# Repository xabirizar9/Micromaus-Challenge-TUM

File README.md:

# Micromaus Best

## Development setup

## Useful Links

[Latex Document](https://latex.tum.de/7947285453qvwcngvsjpdx)

## Datasheets

[L298B](https://www.mouser.de/datasheet/2/389/cd00000240-1795236.pdf)

## Koordinatensysteme 
### Roboter
X zeigt nach vorne, Y nach links, Z nach oben.
Die Y-Achse ist die gemeinsame Drehachse der Motoren, der Ursprung liegt
in der Mitte.

### Welt
Das Weltkoordinatensystem hat seinen Ursprung bei der linken unteren Ecke.
Die X-Achse zeigt nach rechts, die Y-Ache nach oben und die Z-Achse aus
der Ebene heraus.

## Web Interface

To build and run web interface go to `./controller` director and run

```bash
cd ./controller
go build . && ./micromaus

```

Then you can visit the dashboard at [dashboard](http://localhot:8080)

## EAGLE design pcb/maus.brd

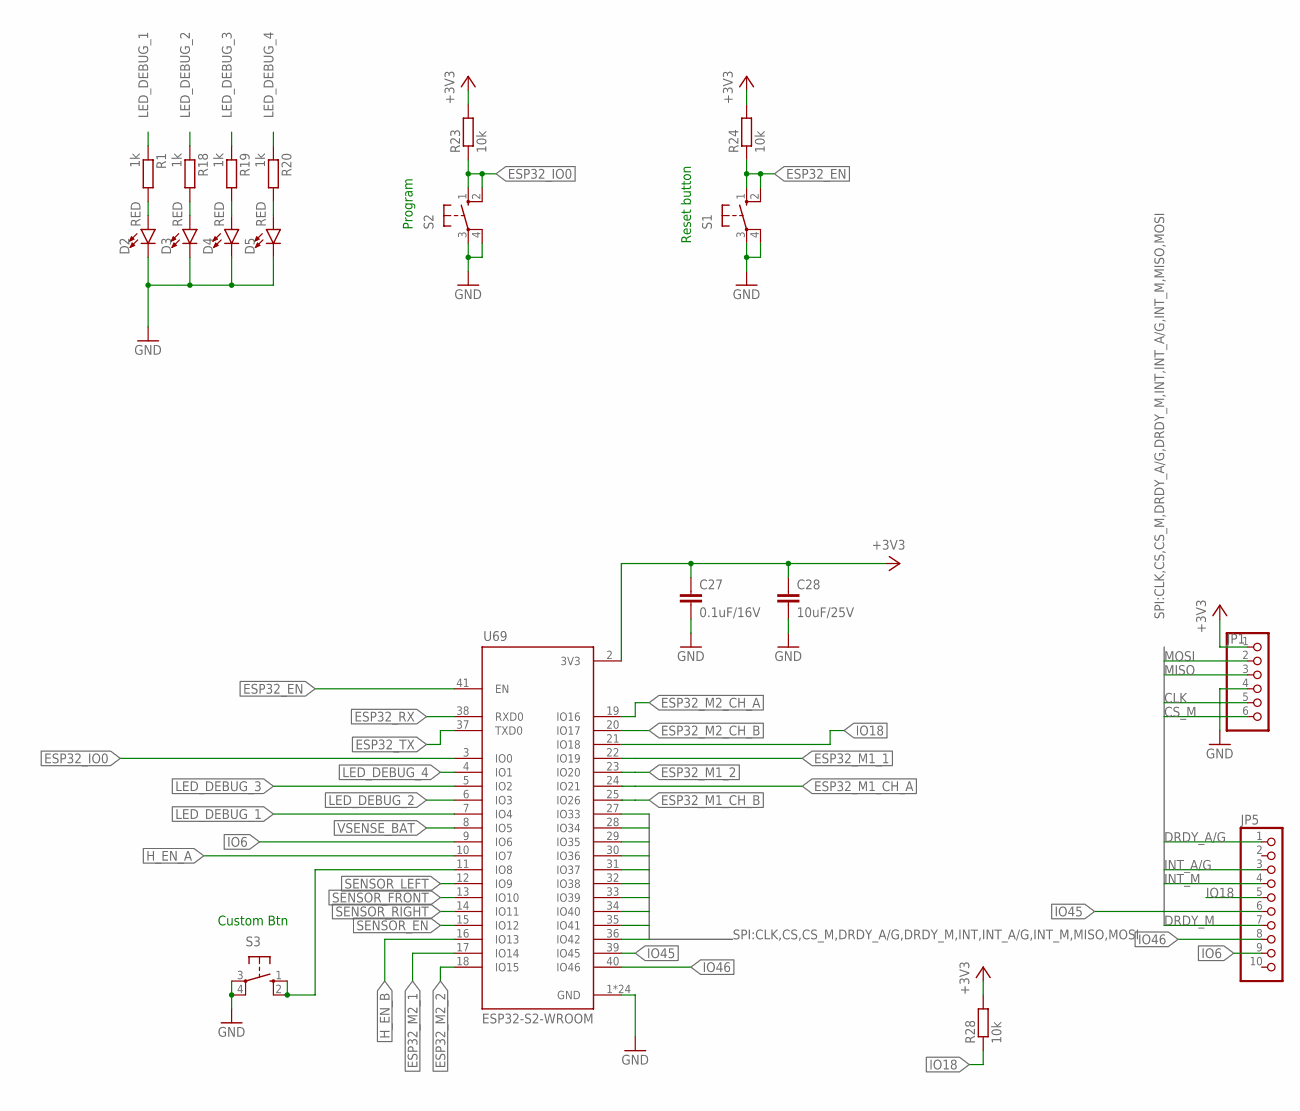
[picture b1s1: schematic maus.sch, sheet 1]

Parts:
C27: 0.1uF/16V; C0805
C28: 10uF/25V; C0805
D2, D3, D4, D5: RED; LED-1206
JP1: PINHD-1X6; 1X06
JP5: PINHD-1X10; 1X10
R1, R18, R19, R20: 1k; R0805
R23, R24, R28: 10k; R0805
S1, S2, S3: 10-XX; B3F-10XX
U69: ESP32-S2-WROOM; XCVR_ESP32-S2-WROOM

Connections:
+3V3: C27.1, C28.1, JP1.1, R23.2, R24.2, R28.2, U69.2 (3V3); also elsewhere on the board
CLK: JP1.5, U69.30 (IO36); also elsewhere on the board
CS: U69.28 (IO34); also elsewhere on the board
CS_M: JP1.6, U69.27 (IO33)
DRDY_A/G: JP5.1, U69.36 (IO42)
DRDY_M: JP5.7, U69.32 (IO38)
ESP32_EN: R24.1, S1.1 (S), S1.2 (S1), U69.41 (EN); also elsewhere on the board
ESP32_IO0: R23.1, S2.1 (S), S2.2 (S1), U69.3 (IO0); also elsewhere on the board
ESP32_M1_1: U69.22 (IO19); also elsewhere on the board
ESP32_M1_2: U69.23 (IO20); also elsewhere on the board
ESP32_M1_CH_A: U69.24 (IO21); also elsewhere on the board
ESP32_M1_CH_B: U69.25 (IO26); also elsewhere on the board
ESP32_M2_1: U69.17 (IO14); also elsewhere on the board
ESP32_M2_2: U69.18 (IO15); also elsewhere on the board
ESP32_M2_CH_A: U69.19 (IO16); also elsewhere on the board
ESP32_M2_CH_B: U69.20 (IO17); also elsewhere on the board
ESP32_RX: U69.38 (RXD0); also elsewhere on the board
ESP32_TX: U69.37 (TXD0); also elsewhere on the board
GND: C27.2, C28.2, D2.C, D3.C, D4.C, D5.C, JP1.4, S1.3, S1.4 (P1), S2.3, S2.4 (P1), S3.3, S3.4 (P1), U69.1 (GND), U69.26 (GND), U69.42 (GND), U69.43.1 (GND), U69.43.2 (GND), U69.43.3 (GND), U69.43.4 (GND), U69.43.5 (GND), U69.43.6 (GND), U69.43.7 (GND), U69.43.8 (GND), U69.43.9 (GND), U69.43.10 (GND), U69.43.11 (GND), U69.43.12 (GND), U69.43.13 (GND), U69.43.14 (GND), U69.43.15 (GND), U69.43.16 (GND), U69.43.17 (GND), U69.43.18 (GND), U69.43.19 (GND), U69.43.20 (GND), U69.43.21 (GND); also elsewhere on the board
H_EN_A: U69.10 (IO7); also elsewhere on the board
H_EN_B: U69.16 (IO13); also elsewhere on the board
INT: U69.33 (IO39); also elsewhere on the board
INT_A/G: JP5.3, U69.35 (IO41)
INT_M: JP5.4, U69.34 (IO40)
IO6: JP5.9, U69.9 (IO6)
IO18: JP5.5, R28.1, U69.21 (IO18)
IO45: JP5.6, U69.39 (IO45)
IO46: JP5.8, U69.40 (IO46)
LED_DEBUG_1: R1.1, U69.7 (IO4)
LED_DEBUG_2: R18.1, U69.6 (IO3)
LED_DEBUG_3: R19.1, U69.5 (IO2)
LED_DEBUG_4: R20.1, U69.4 (IO1)
MISO: JP1.3, U69.31 (IO37); also elsewhere on the board
MOSI: JP1.2, U69.29 (IO35); also elsewhere on the board
unnamed: S3.1 (S), S3.2 (S1), U69.11 (IO8)
unnamed: D2.A, R1.2
unnamed: D3.A, R18.2
unnamed: D4.A, R19.2
unnamed: D5.A, R20.2
SENSOR_EN: U69.15 (IO12); also elsewhere on the board
SENSOR_FRONT: U69.13 (IO10); also elsewhere on the board
SENSOR_LEFT: U69.12 (IO9); also elsewhere on the board
SENSOR_RIGHT: U69.14 (IO11); also elsewhere on the board
VSENSE_BAT: U69.8 (IO5); also elsewhere on the board

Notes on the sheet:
Reset button
Program
Custom Btn

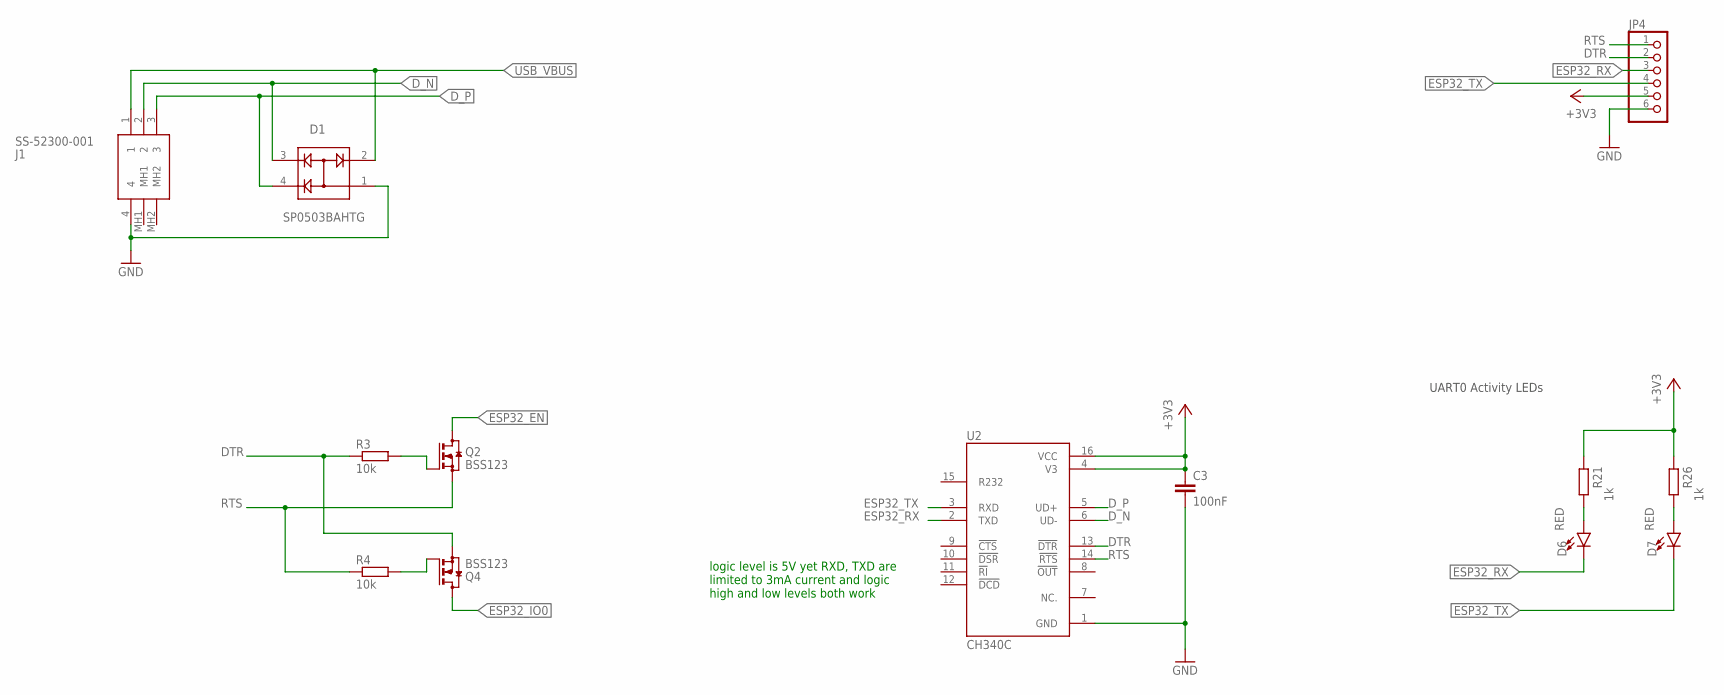
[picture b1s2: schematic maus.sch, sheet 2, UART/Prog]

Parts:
C3: 100nF; C0805
D1: SP0503BAHTG; SOT143
D6, D7: RED; LED-1206
J1: SS-52300-001; SS52300001
JP4: PINHD-1X6; 1X06
Q2, Q4: BSS123; SOT23
R3, R4: 10k; R0805
R21, R26: 1k; R0805
U2: CH340C; SOIC127P600X180-16N

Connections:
+3V3: C3.1, JP4.5, R21.2, R26.2, U2.4 (V3), U2.16 (VCC); also elsewhere on the board
DTR: JP4.2, Q4.2 (S), R3.1, U2.13 (!DTR)
D_N: D1.3, J1.2, U2.6 (UD-)
D_P: D1.4, J1.3, U2.5 (UD+)
ESP32_EN: Q2.3 (D); also elsewhere on the board
ESP32_IO0: Q4.3 (D); also elsewhere on the board
ESP32_RX: D6.C, JP4.3, U2.2 (TXD); also elsewhere on the board
ESP32_TX: D7.C, JP4.4, U2.3 (RXD); also elsewhere on the board
GND: C3.2, D1.1, J1.4, JP4.6, U2.1 (GND); also elsewhere on the board
unnamed: Q2.1 (G), R3.2
unnamed: Q4.1 (G), R4.2
unnamed: D6.A, R21.1
unnamed: D7.A, R26.1
RTS: JP4.1, Q2.2 (S), R4.1, U2.14 (!RTS)
USB_VBUS: D1.2, J1.1; also elsewhere on the board

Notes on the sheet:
UART0 Activity LEDs
logic level is 5V yet RXD, TXD are limited to 3mA current and logic high and low levels both work

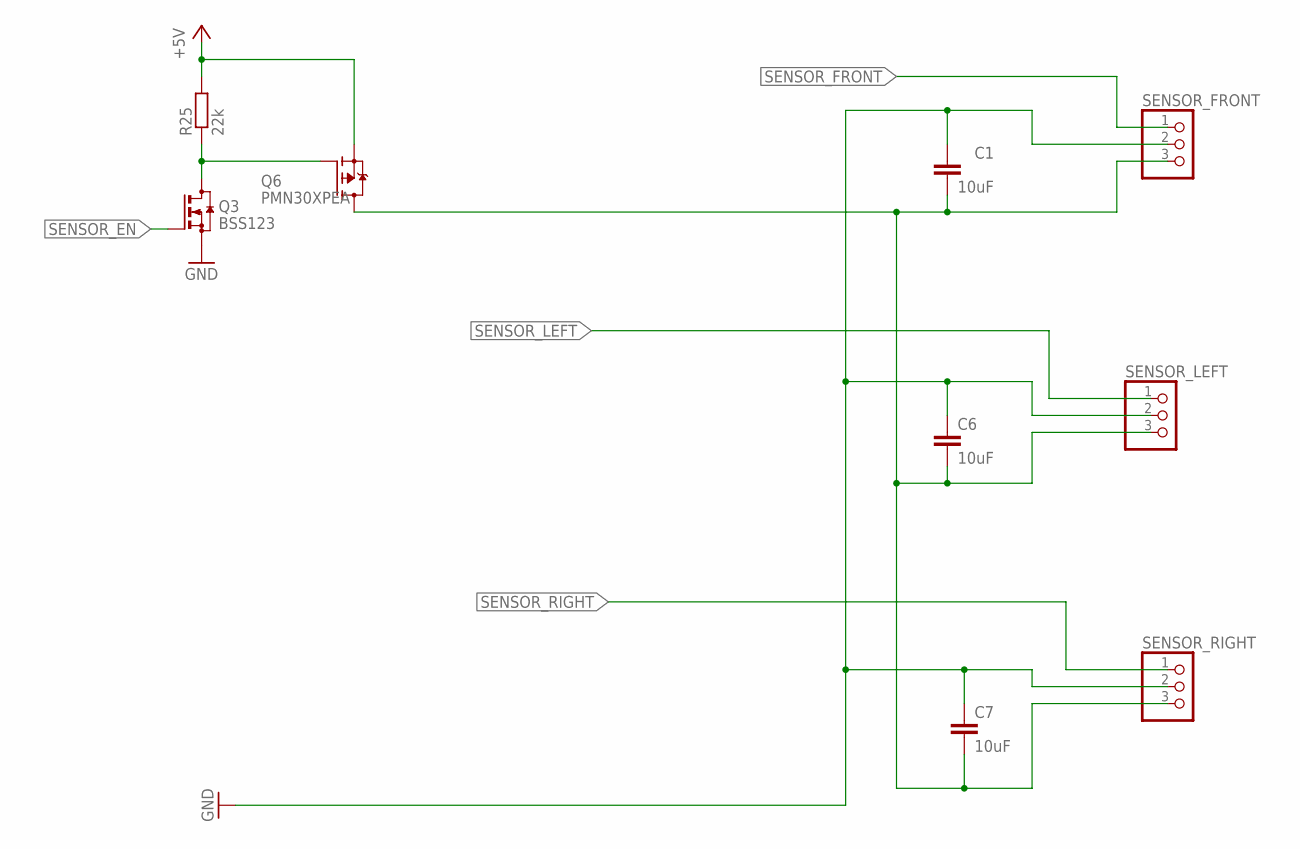
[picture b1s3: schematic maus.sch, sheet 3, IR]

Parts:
C1, C6, C7: 10uF; C0805
Q3: BSS123; SOT23
Q6: PMN30XPEA; SOT95P255X110-6N
R25: 22k; R0805
SENSOR_FRONT: PINHD-1X3; 1X03
SENSOR_LEFT: PINHD-1X3; 1X03
SENSOR_RIGHT: PINHD-1X3; 1X03

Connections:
+5V: Q6.4 (S), R25.2; also elsewhere on the board
GND: C1.1, C6.1, C7.1, Q3.2 (S), SENSOR_FRONT.2, SENSOR_LEFT.2, SENSOR_RIGHT.2; also elsewhere on the board
unnamed: Q3.3 (D), Q6.3 (G), R25.1
unnamed: C1.2, C6.2, C7.2, Q6.1 (D), Q6.2 (D), Q6.5 (D), Q6.6 (D), SENSOR_FRONT.3, SENSOR_LEFT.3, SENSOR_RIGHT.3
SENSOR_EN: Q3.1 (G); also elsewhere on the board
SENSOR_FRONT: SENSOR_FRONT.1; also elsewhere on the board
SENSOR_LEFT: SENSOR_LEFT.1; also elsewhere on the board
SENSOR_RIGHT: SENSOR_RIGHT.1; also elsewhere on the board

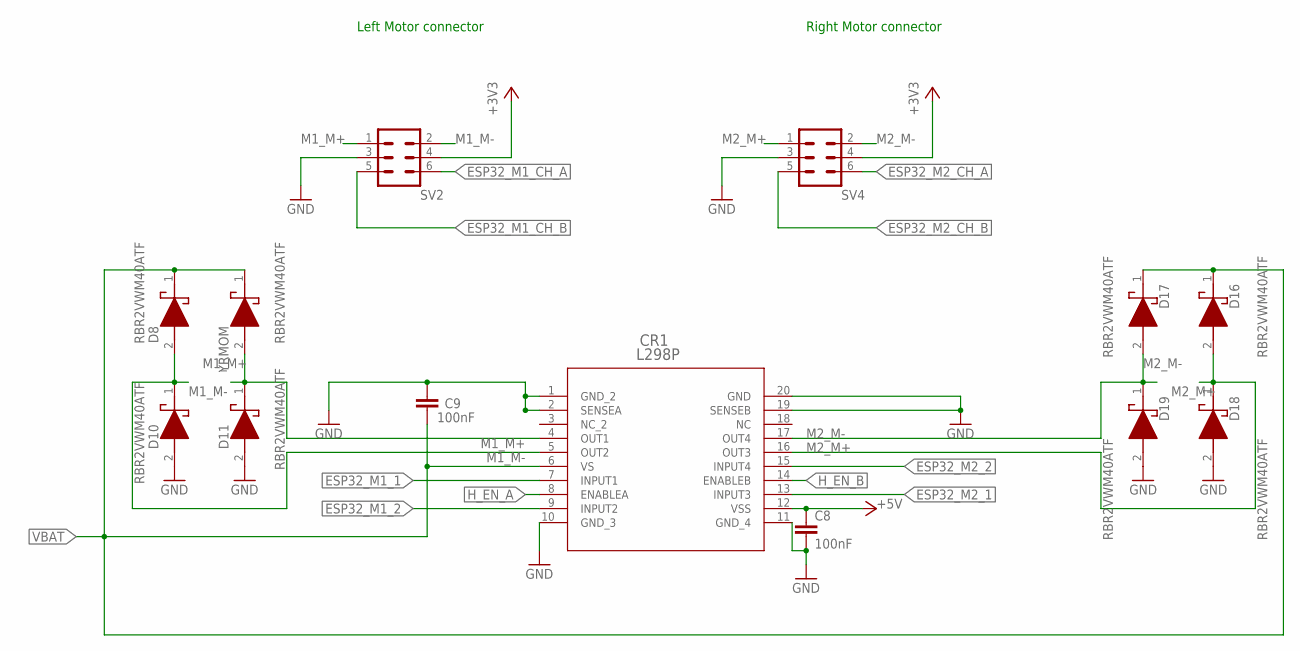
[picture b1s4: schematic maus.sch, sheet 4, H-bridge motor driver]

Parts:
C8, C9: 100nF; C0805
CR1: L298P; POWERSO-20_STM
D8, D10, D11, D16, D17, D18, D19: RBR2VWM40ATF; RB068VWM100
SV2, SV4: ML6
YRMOM: RBR2VWM40ATF; RB068VWM100

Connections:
+3V3: SV2.4, SV4.4; also elsewhere on the board
+5V: C8.1, CR1.12 (VSS); also elsewhere on the board
ESP32_M1_1: CR1.7 (INPUT1); also elsewhere on the board
ESP32_M1_2: CR1.9 (INPUT2); also elsewhere on the board
ESP32_M1_CH_A: SV2.6; also elsewhere on the board
ESP32_M1_CH_B: SV2.5; also elsewhere on the board
ESP32_M2_1: CR1.13 (INPUT3); also elsewhere on the board
ESP32_M2_2: CR1.15 (INPUT4); also elsewhere on the board
ESP32_M2_CH_A: SV4.6; also elsewhere on the board
ESP32_M2_CH_B: SV4.5; also elsewhere on the board
GND: C8.2, C9.2, CR1.1 (GND_2), CR1.2 (SENSEA), CR1.10 (GND_3), CR1.11 (GND_4), CR1.19 (SENSEB), CR1.20 (GND), D10.2 (A), D11.2 (A), D18.2 (A), D19.2 (A), SV2.3, SV4.3; also elsewhere on the board
H_EN_A: CR1.8 (ENABLEA); also elsewhere on the board
H_EN_B: CR1.14 (ENABLEB); also elsewhere on the board
M1_M+: CR1.4 (OUT1), D11.1 (K), SV2.1, YRMOM.2 (A)
M1_M-: CR1.5 (OUT2), D8.2 (A), D10.1 (K), SV2.2
M2_M+: CR1.16 (OUT3), D16.2 (A), D18.1 (K), SV4.1
M2_M-: CR1.17 (OUT4), D17.2 (A), D19.1 (K), SV4.2
VBAT: C9.1, CR1.6 (VS), D8.1 (K), D16.1 (K), D17.1 (K), YRMOM.1 (K); also elsewhere on the board

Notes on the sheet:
Left Motor connector
Right Motor connector

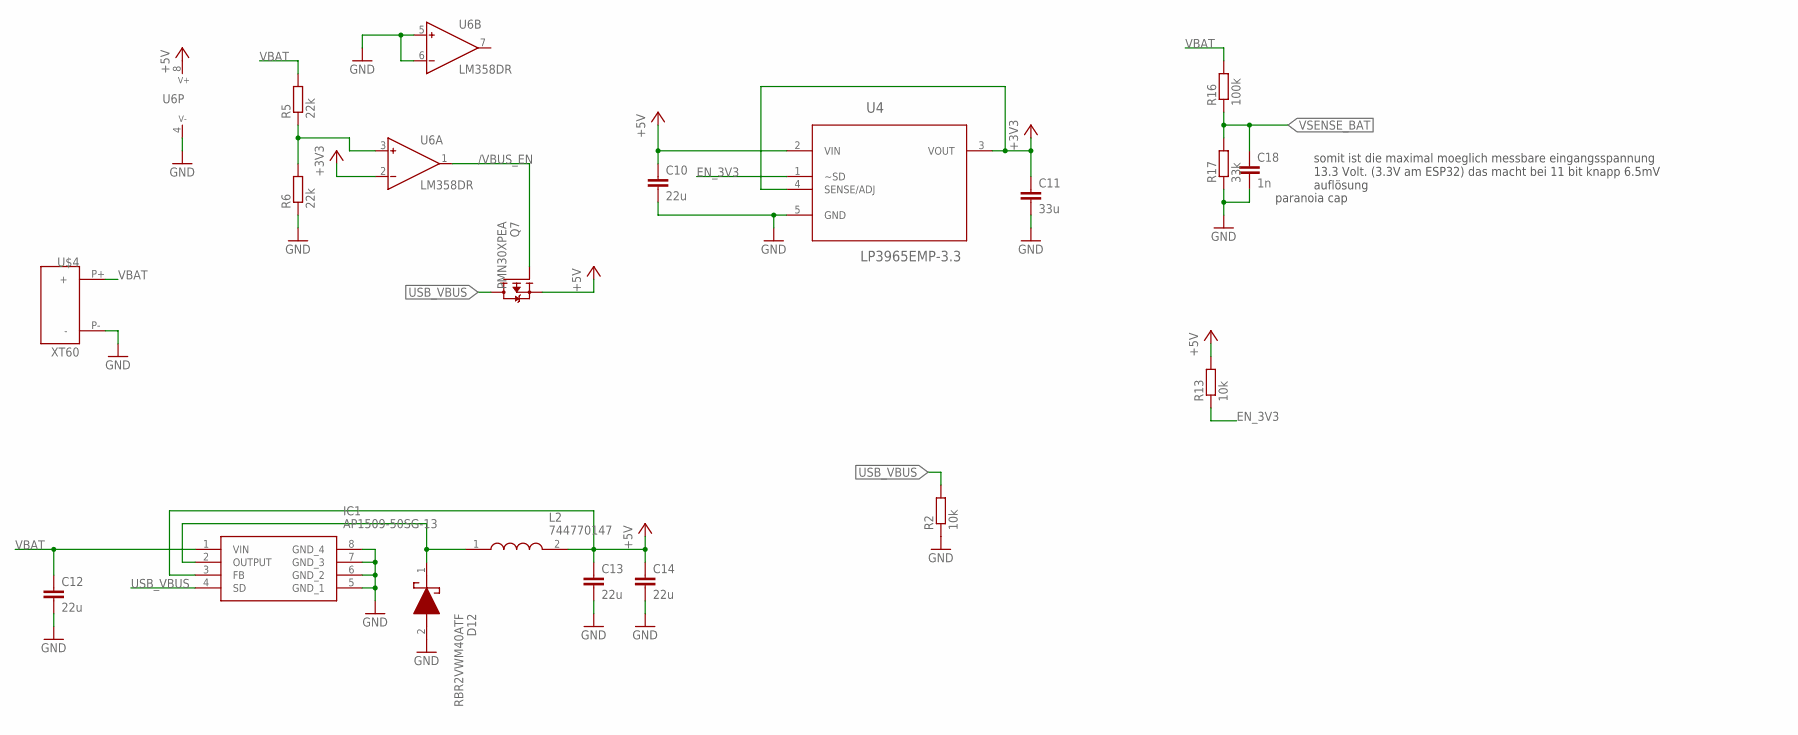
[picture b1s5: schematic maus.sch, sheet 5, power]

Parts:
C10, C12, C13, C14: 22u; C0805
C11: 33u; C0805
C18: 1n; C0805
D12: RBR2VWM40ATF; RB068VWM100
IC1: AP1509-50SG-13; SOIC127P600X175-8N
L2: 744770147; WE-PD_1260/1245/1280/121054
Q7: PMN30XPEA; SOT95P255X110-6N
R2, R13: 10k; R0805
R5, R6: 22k; R0805
R16: 100k; R0805
R17: 33k; R0805
U4: LP3965EMP-3.3; SOT150P696X180-5N
U6: LM358DR; SOIC127P610X175-8N
U$4: XT60; XT60-UPRIGHT

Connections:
+3V3: C11.1, U4.3 (VOUT), U4.4 (SENSE/ADJ), U6.2 (IN-); also elsewhere on the board
+5V: C10.1, C13.1, C14.1, IC1.3 (FB), L2.2, Q7.4 (S), R13.2, U4.2 (VIN), U6.8 (V+); also elsewhere on the board
/VBUS_EN: Q7.3 (G), U6.1 (OUT)
EN_3V3: R13.1, U4.1 (~SD)
GND: C10.2, C11.2, C12.2, C13.2, C14.2, C18.2, D12.2 (A), IC1.5 (GND_1), IC1.6 (GND_2), IC1.7 (GND_3), IC1.8 (GND_4), R2.1, R6.1, R17.1, U4.5 (GND), U6.4 (V-), U6.5 (IN+), U6.6 (IN-), U$4.P- (-); also elsewhere on the board
unnamed: D12.1 (K), IC1.2 (OUTPUT), L2.1
unnamed: R5.1, R6.2, U6.3 (IN+)
USB_VBUS: IC1.4 (SD), Q7.1 (D), Q7.2 (D), Q7.5 (D), Q7.6 (D), R2.2; also elsewhere on the board
VBAT: C12.1, IC1.1 (VIN), R5.2, R16.2, U$4.P+ (+); also elsewhere on the board
VSENSE_BAT: C18.1, R16.1, R17.2; also elsewhere on the board

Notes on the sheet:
somit ist die maximal moeglich messbare eingangsspannung 13.3 Volt. (3.3V am ESP32) das macht bei 11 bit knapp 6.5mV auflösung
paranoia cap

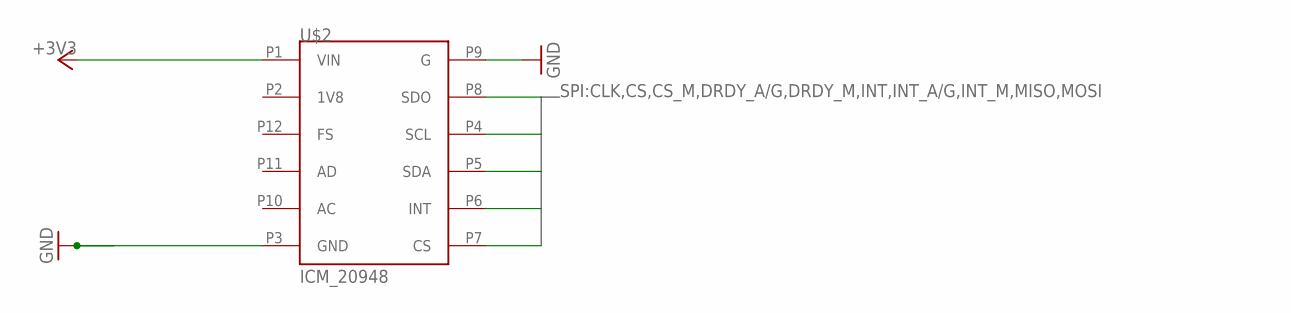
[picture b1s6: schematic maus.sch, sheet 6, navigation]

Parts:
U$2: ICM_20948; ICM_20948-F

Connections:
+3V3: U$2.P1 (VIN); also elsewhere on the board
CLK: U$2.P4 (SCL); also elsewhere on the board
CS: U$2.P7 (CS); also elsewhere on the board
GND: U$2.P3 (GND), U$2.P9 (G); also elsewhere on the board
INT: U$2.P6 (INT); also elsewhere on the board
MISO: U$2.P8 (SDO); also elsewhere on the board
MOSI: U$2.P5 (SDA); also elsewhere on the board

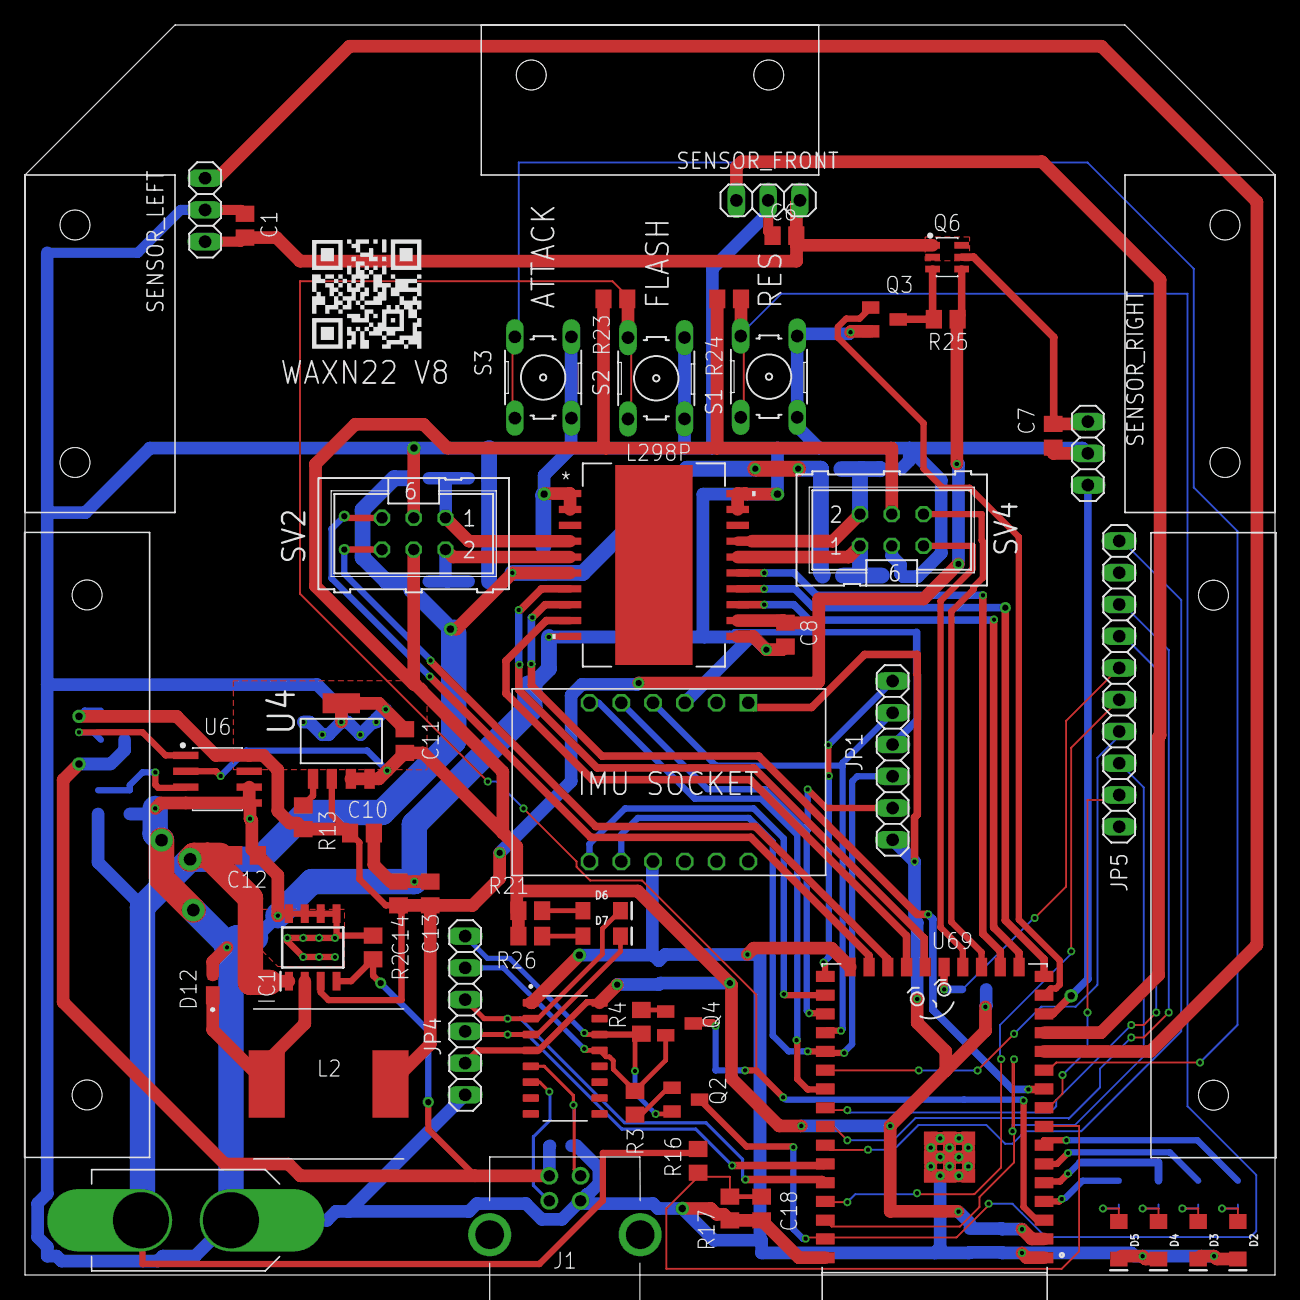
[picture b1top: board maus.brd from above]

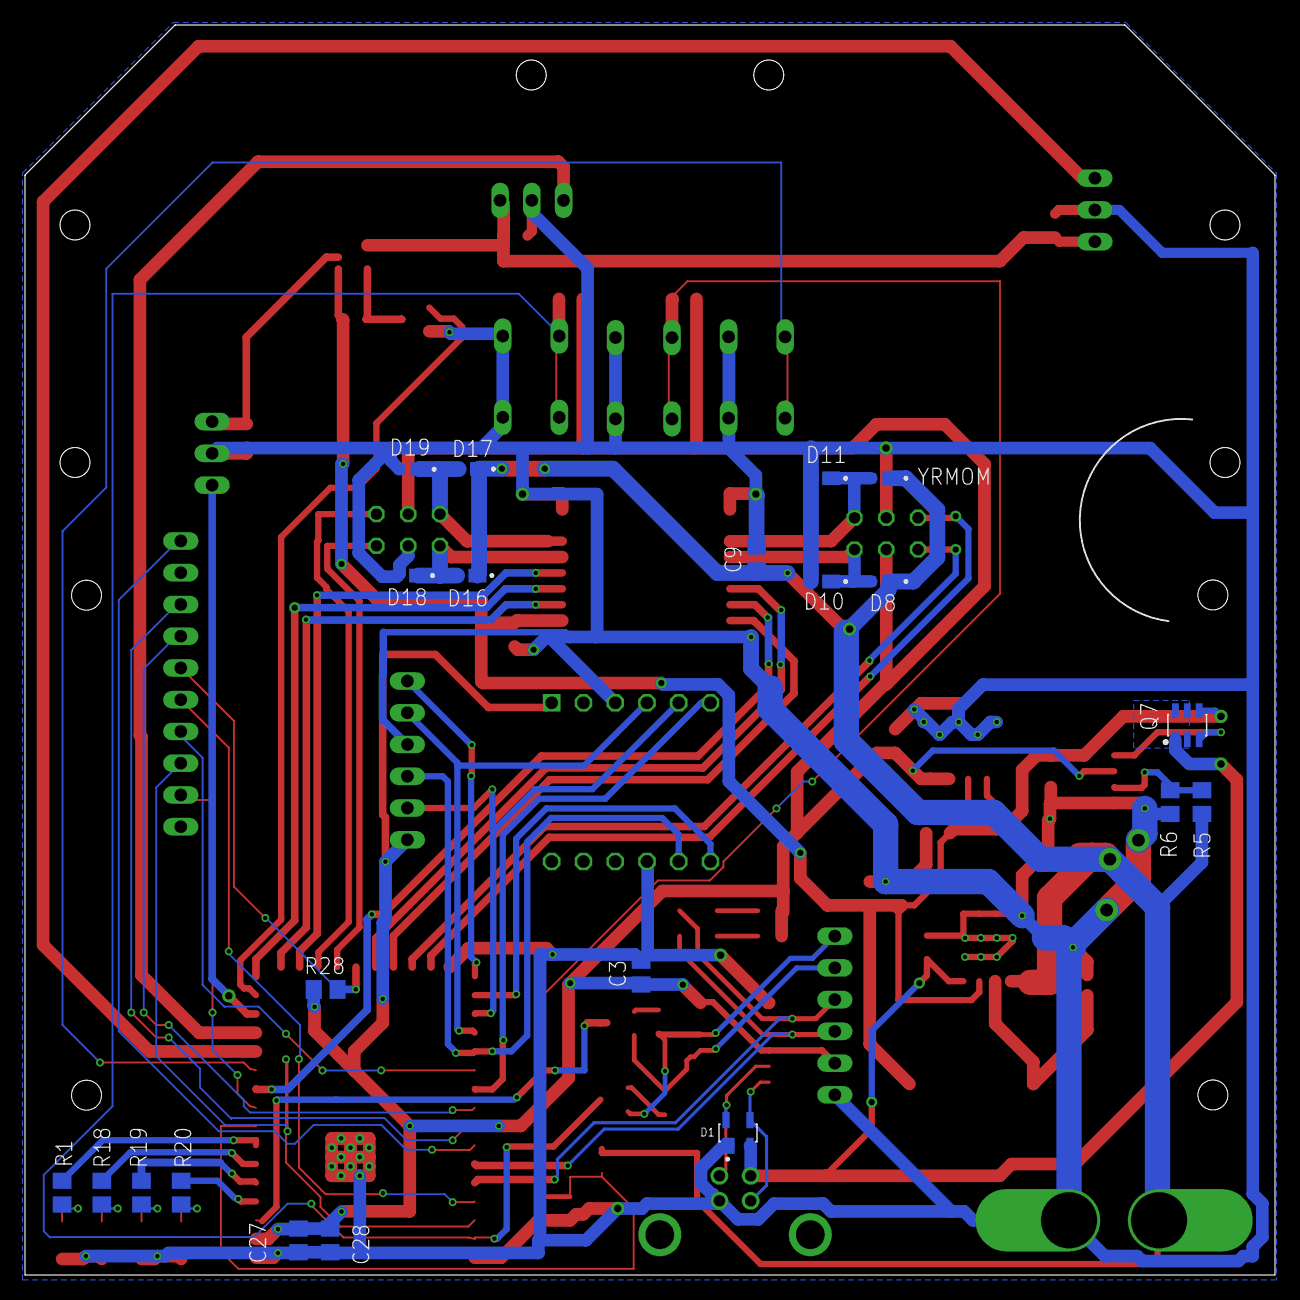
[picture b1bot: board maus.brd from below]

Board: 2 copper layers, 100.0 x 100.0 mm, 79 parts (21 on the bottom side), 65 nets.

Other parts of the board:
U$1, U$3: MOTOR_HALTERUNG
U$6, U$7, U$8: SENSOR_HALTERUNG

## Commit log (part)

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2022-03-17 added calibration measurements spreadsheet
2022-03-17 added a config.h for pin numbers
2022-03-17 needed to get over adc code from Sensors_tests
2022-03-17 deleted ADC2 which can't be used, adc reading now reports millivolts
2022-03-17 optimization: we need no reference to the adc
2022-03-18 renamed voltage_measurements.ods -> versuchsreihen.ods
2022-03-18 fix: clang golang format
2022-03-18 fix: buffer issues in UDP streamer
2022-03-18 added some fits for the ir sensor measurements
2022-03-18 added power::VoltageGauge and power::Battery classes
2022-03-18 now uses correct millivolt readings
2022-03-18 PowerManagement class / thread
2022-03-18 adds PowerManagement to main task
2022-03-18 can now establish i2c connection to module
2022-03-18 some more i2c ICM things
2022-03-18 save current register bank so we don't repeatedly switch to the same bank
2022-03-18 added missing things, mist
2022-03-18 (untested) added acceleration reading
2022-03-18 more spi things
2022-03-18 SPI classes
2022-03-18 yeah templates rock
2022-03-18 fixed SPI comms
2022-03-18 (wip) added IMU init functions
2022-03-18 added 16 bit SPI r/w functions
2022-03-18 fixup! (untested) added acceleration reading
2022-03-18 ignore some more types of generated files
2022-03-18 added ICM20948 Gyro range setting and reading in physical units (deg per sec)
2022-03-18 can now setup the magnetometer, reading it still doesn't work
2022-03-18 added all icm registers
2022-03-18 ICM20948::readAccel now uses linalg::Vec divide operator
2022-03-18 added readMag in microtesla units
2022-03-18 fix: i2c master reads data (instead of writing)
2022-03-18 (wip) magnetometer startup
2022-03-18 added buffer reading capablilites to SPI
2022-03-18 added accelerometer reading in physical units (of G)
2022-03-18 readAccelRaw now uses buffer read, added readGyroRaw, readTempRaw
2022-03-18 fix: magnetometer endianness
2022-03-18 added temperature reading in celsius
2022-03-18 added mathematical operations to linalg::Vec
2022-03-18 made SPI compatible with S2
2022-03-18 gpio numbers for SPI
2022-03-19 added Motor class
2022-03-19 added LEDCChannelResource shared resource
2022-03-20 feat: add general controller class
2022-03-20 feat: add basic PID controller
2022-03-21 add: protokoll, copied my bachelor thesis preamble
2022-03-22 minor changes
2022-03-22 reordered hpp file
2022-03-22 correct PID controller
2022-03-22 corrected controller
2022-03-22 wip: PID
2022-03-22 feat: add initial PID setup
2022-03-22 koordinatensystem im README
2022-03-22 Sensor
2022-03-22 new lane control task
2022-03-22 small update
2022-03-23 feat: enable 802.1x with eduroam
2022-03-23 feat: add 802.1x support
2022-03-23 fix: revert changes to controller
2022-03-23 feat: add hook
2022-03-23 fix: enable formatter
2022-03-23 feat: update net manager
2022-03-23 feat: update rendering
2022-03-23 feat: send commands via go to robot
2022-03-23 feat: update
2022-03-24 feat: add static html
2022-03-24 feat: include more robot info
2022-03-24 feat: update message reading for longer commands
2022-03-24 feat: update layout
2022-03-24 modell für ir-sensor
2022-03-24 added Map belief distribution representation
2022-03-24 clang-format
2022-03-24 draft for Mapper (class with methods that update the belief)
2022-03-24 fixup! draft for Mapper (class with methods that update the belief)
2022-03-25 feat: update PID & add ping-pong
2022-03-25 feat: add ping pong
2022-03-25 feat: update proto
2022-03-25 Sensorupdate
2022-03-25 added clamp function and linecontrol PID
2022-03-25 small changes
2022-03-25 solved conflicts
2022-03-25 feat: add config to maus
2022-03-25 cm to mm
2022-03-25 added my whole literature database lol
2022-03-25 added TOC
2022-03-25 fix: format
2022-03-25 fix: not building
2022-03-25 removed binary
2022-03-25 turn right
2022-03-25 shitty conflicts
2022-03-25 removed unused variables0
2022-03-25 wrote something about hardware
2022-03-25 modified variable names and removed template
2022-03-25 feat: extend proto
2022-03-25 turn
2022-03-25 turnOnspot
2022-03-25 bleh
2022-03-25 added schematic as appendix
2022-03-25 camel case
2022-03-26 fixed date in title
2022-03-26 fixed makefile, now uses *.tex glob as dependencies
2022-03-26 more text about hardware, sensors, h-bridge, power supply, low-power mode
2022-03-26 feat: implement reconnect + refactor frontend
2022-03-26 feat: update controller
2022-03-27 feat: update frontend
2022-03-28 feat: cleanup tasks
2022-03-28 wip: auto PID tunner
2022-03-28 WIP: add auto tune test
2022-03-28 feat: remove logs
2022-03-28 feat: improve speed change
2022-03-29 feat: update web
2022-03-29 wip: add steering
2022-03-29 wip: add maze explorer
2022-03-29 feat: add driver
2022-03-29 wip: drive controlls
2022-03-29 feat: update cmd model
2022-03-29 feat: add UDP receiver server
2022-03-29 added turning radius functionality
2022-03-29 feat: add remote connector interface
2022-03-29 made time interval static
2022-03-29 if radius is negative, division should still take positive R
2022-03-29 simplified equation
2022-03-29 feat: update speed
2022-03-29 feat: add joystick controlls
2022-03-29 feat: add remote discovery
2022-04-01 temp
2022-04-01 removed comment
2022-04-02 feat: add drive events
2022-04-03 feat: refactor classes
2022-04-03 changed lanetask direction
2022-04-03 update2
2022-04-03 feat: switch to relative dead reconning
2022-04-03 feat: add set position
2022-04-03 feat: regenerate
2022-04-03 drivetaskupdate
2022-04-03 feat: update types
2022-04-03 "switchrepair"
2022-04-03 feat: update readme
2022-04-03 feat: open in browser
2022-04-03 "movecell with encoder"
2022-04-03 feat: update controlls
2022-04-03 feat: add wip navigation
2022-04-03 feat: update position
2022-04-03 feat: add keyboard
2022-04-03 feat: add auto open browser
2022-04-04 feat: add fill to maze solver
2022-04-04 feat: update coordinates
2022-04-04 feat: add debug logs
2022-04-04 feat: remove hardcoded cmd
2022-04-04 feat: update remote solver start
2022-04-04 feat: update stuff
2022-04-04 "io"
2022-04-04 "speedcorrection"
2022-04-04 added nav::Heading, a unification for robot direction, also for Maze and MapBelief class
2022-04-04 ok that was a bad idea, now uses enum CardinalDirection
2022-04-04 CardinalDirection now a class, using operators (i hope this is final)
2022-04-04 Maze and MazeSolver now using new CardinalDirection
2022-04-04 MapBelief now uses nav::CardinalDirection
2022-04-04 refactor: MapBelief has more complex implementations now in MapBelief.cpp
2022-04-04 added scripts/format-modified.sh which formats all modified c++ files
2022-04-04 moved RobotPosition to nav/Position.hpp
2022-04-04 feat: send solver state to client
2022-04-04 feat: enable drive commands
2022-04-04 feat: update frontend to show direction
2022-04-04 feat: update title
2022-04-04 "drivetask"
2022-04-05 ran clang-format
2022-04-05 added script scripts/check-staged-format.sh to check for changes that introduce formatting errors, useful as a pre-commit hook
2022-04-05 fix: check-staged-format does not ignore new files
    fix: check-staged-format works even if no c/hpp files added
2022-04-05 (wip) a little bit of structure for the filter
2022-04-05 Vec: now has Row number template argument
2022-04-05 feat: add discovery service
2022-04-05 Vec is now a kind of Mat
2022-04-05 moved matrix-scalar ops into separate file
2022-04-05 added matrix-matrix multiplication and vector dot product
2022-04-05 added type shorthands for Vec2/3f and Mat3f
2022-04-05 fixup! added type shorthands for Vec2/3f and Mat3f
2022-04-05 "lanecontroll"
2022-04-05 added easier Vec3f and Vec2f constructors
2022-04-05 everything now uses new vector types
2022-04-05 "IRtest"
2022-04-05 error
2022-04-05 feat: add update sensors
2022-04-05 feat: typo
2022-04-05 feat: init wall detection
2022-04-05 nomore offset
2022-04-05 feat: add lane callibration
2022-04-05 feat: use config
2022-04-05 added vec2f cross product
2022-04-05 feat: update lane controll
2022-04-05 feat: update PID
2022-04-05 feat: clear events when recv command completion
2022-04-06 feat: sync PIDs
2022-04-06 feat: update drive handling
2022-04-06 added RobotPositionDistribution class for gaussian robot positions
2022-04-06 Location header now uses RobotPositionDistribution class
2022-04-06 feat: update selection
2022-04-06 feat: add variable correction
2022-04-06 time function
2022-04-06 feat: remove comment
2022-04-06 fix: streaming
2022-04-06 fixed references to namespace linalg in POsition.hpp
2022-04-06 added matrix <- array assignment, x/y/z access functions, vector to diag matrix
2022-04-06 added angle constants
2022-04-06 implemented extended kalman prediction step
2022-04-06 added pin() method to set standard deviations to zero
2022-04-06 laneimproved
2022-04-06 feat: allow smaller changes
2022-04-06 feat: add template
2022-04-06 added SLAM update to Controller
2022-04-06 feat: fix stuff
2022-04-06 feat: add checks
2022-04-06 added PosDistribution message and such a field to NavigationPacket
2022-04-06 copy position distribution to state
2022-04-06 feat: update data
2022-04-06 feat: log nav packets
2022-04-06 feat: make it work
2022-04-06 feat: add delay
2022-04-06 feat: update costs
2022-04-06 feat: add more logs
2022-04-06 message
2022-04-06 edsjoidso
2022-04-06 created class for handling motion profiles
2022-04-06 feat: add go home
2022-04-06 feat: remove delay
2022-04-06 skrfh
2022-04-06 feat: nav
2022-04-07 wip: log commands when driving
2022-04-07 feat: add controlInterval const
2022-04-07 add stuff
2022-04-07 compute velocity profile for straight lines
2022-04-07 removed motion profile from drive task
2022-04-07 worked on motion profiles
2022-04-08 solved scaling issue
2022-04-08 changed trajectory formula to craig's book
2022-04-08 implemented motion profile methods
2022-04-08 feat: wip remote server update
2022-04-09 feat: add reconnect
2022-04-09 feat: move com to client obj
2022-04-11 feat: update handling
2022-04-11 feat: improve stuff
2022-04-11 wip: lane + PID improvements
2022-04-12 feat: do stuff
2022-04-12 feat: implement motion profile
2022-04-12 fix stuff
2022-04-12 feat: add logs
2022-04-12 added fixes for motion profiles
2022-04-12 feat: tune pid
2022-04-13 solved merge conflicts
2022-04-15 fixed things for motion profile
2022-04-15 MM_Report
2022-04-15 motion profile fixes
2022-04-15 Deleted .gitlab-ci.yml
2022-04-16 wip: add auto tuner
2022-04-16 feat: drive straight
2022-04-16 feat: update commands
2022-04-16 fix: cmd memory issue
2022-04-16 feat: motion profiles
2022-04-16 FEAT: add profile
2022-04-16 feat: motion profile handling
2022-04-16 added subclasses
2022-04-16 feat: integrate profiles
2022-04-16 finished switch cases and fixed turnonspot
2022-04-16 feat: update messages
2022-04-17 fixed not building
2022-04-17 fix: motion profiles
2022-04-17 now curve profiles can be created for curves with given radius and angle
2022-04-17 fixed fall through
2022-04-17 fix: adapted distance driven in grid profiles to avoid overshooting
2022-04-17 made motion profiles in mm
2022-04-17 feat: include changes
2022-04-17 fix: grid cell computation
2022-04-17 feat: add drive curves
2022-04-17 feat: enable true fast run
2022-04-18 fixed Callibration typo
2022-04-26 ADC: universally compilable bit width
2022-04-28 changed wheel distance
2022-04-28 add static IP option
2022-04-28 fixes
2022-04-28 fix: added correction at end of moveCells
2022-04-28 fixed
2022-04-28 feat: update solver
2022-04-28 fix: driving
2022-04-28 pid refactor + use pid instead of motion profile for MoveCells
2022-04-28 fixed max speed
2022-04-28 fixed mp
2022-04-28 feat: path finding
2022-04-28 updated intervals in drivetask
2022-04-28 feat: fix turning left
2022-04-28 tuned MoveCells PID value
2022-04-28 fix: heading stuff
2022-04-28 fix: time interval counters
2022-04-28 commented logs
2022-04-28 speed change
2022-04-28 add walls
2022-04-28 walls
2022-08-09 Removed spionage from git history

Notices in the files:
parts and their libraries:
SparkFun-LED: Licensing: Creative Commons ShareAlike 4.0 International - https://creativecommons.org/licenses/by-sa/4.0
COPYRIGHT: Copyright (C) 2022 Ultra Librarian. All rights reserved.
